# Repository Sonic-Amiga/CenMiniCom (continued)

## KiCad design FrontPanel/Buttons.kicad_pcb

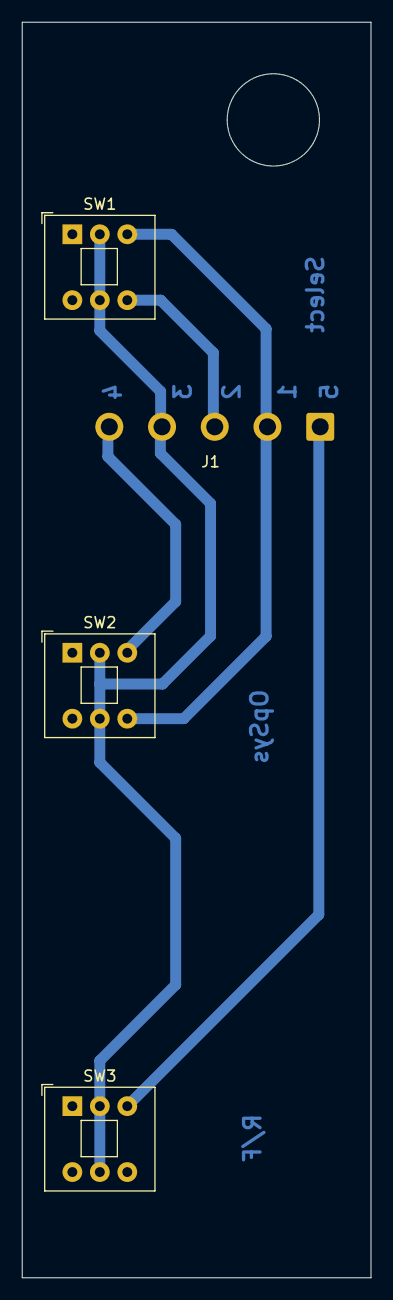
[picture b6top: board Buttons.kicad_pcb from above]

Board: 2 copper layers, 31.8 x 114.3 mm, 4 parts (0 on the bottom side), 5 nets.

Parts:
J1: Conn_01x05_Female; SolderWire-0.75sqmm_1x05_P4.8mm_D1.25mm_OD2.3mm
SW1: SELECT; SW_Push_2P2T_Toggle_CK_PVA2xxH1xxxxxxV2
SW2: OPSYS; SW_Push_2P2T_Toggle_CK_PVA2xxH1xxxxxxV2
SW3: R/F; SW_Push_2P2T_Toggle_CK_PVA2xxH1xxxxxxV2

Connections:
unnamed: J1.4, SW1.2 (B), SW1.5 (B), SW2.2 (B), SW2.5 (B), SW3.2 (B), SW3.5 (B)
unnamed: J1.2, SW1.3 (C), SW2.6 (C)
unnamed: J1.3, SW1.6 (C)
unnamed: J1.5, SW2.3 (C)
unnamed: J1.1, SW3.3 (C)

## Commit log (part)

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2022-08-10 CPU: Part replacement
    Some parts are not available, replaced with analogs
2022-08-11 CPU: Replace 8835
    This part isn't available at all; so let's replace it with ls240 + ls244. ls240
    looks the most electrically compatible in terms of current loads.
2022-08-15 Get rid of 74ls378
    This chip is rather rare and expensive here. Three can be replaced by 74ls379;
    use 74ls377 instead of the remaining one (ALU flags register)
    Analogs list populated and changed to a more proper encoding
2022-08-16 Replace edge connector with pin headers
2022-08-16 Attempt to fix a table
2022-08-17 CPU: Part placement
    Place parts on the board, no routing yet
2022-08-18 Fix ISA ROM designation
    Replace russian 'C' letter with latin one. They look identical but have
    different codes and UTF-8 characters in the .dsn file cause FreeRouting's
    loader to crash
2022-08-19 Manual layout WIP
    Attempt on manually-assisted layout. This uncovers some opportunities for
    optimization.
2022-08-19 Changed twist on uCode read buffers
    This yields much more optimal PCB layout
2022-08-20 More schematic optimizations:
    - Constant gate pins rearranged
    - Disconnected P7.14 from uROM override. The connector is located too far, the
    track is not convenient to route
2022-08-20 Changed U_M7 pin assignments
    Now lays out straight
2022-08-21 Another checkpoint
    Arranging the parts back does have some success, it's now time to try to replace
    some of them with SOIC.
2022-08-21 DIP layout prototype
    Parts arranged
2022-08-21 Part of routed layout
    A successful manually routed part: sequencer ROMs and buffers.
2022-08-21 Optimized connections around R7
    Removed debugging connections, switched pins around for straight tracks.
    Some inverters optimized away due to debug harness removal
2022-08-21 Revert back to Centurion edge connector
    Since i've found original connectors, there's no reason for substitution
2022-08-21 Some PoC routing near the bus connector
    A checkpoint, i'll try moving chips around in order to optimize tracks
2022-08-22 Routing WIP
    Checkpoint
2022-08-24 Some power lines
    Proof of concept - can i really do it ?
2022-08-25 Substitute RN16
    A dual 330+220 ohm resistor network appears to only be available in DIP package
    here; additionally having these resistors in one assembly requires more long
    traces, which are very inconvenient in connector area as both layers are quite
    busy. Break it down into individual parts.
2022-08-26 Swap U_B11C inputs
    Lays out much better
2022-08-28 Rounting WIP
    Second row almost done.
2022-08-28 Second row completed
2022-08-31 More layout
    3rd row ~75% completed
2022-09-01 4rth row placement
    PoC placement, optimized tracks layout, Result bus moved to the right side. A
    checkpoint before moving the whole row.
2022-09-01 Move completed
    Now we have much more space between 4th and 5th rows for tracks
2022-09-02 Remove P10
    This diagnostics connector gives direct access to page table DRAM, we don't need
    it. In fact it could have been located in B row with much shorter traces, but
    the only available position there is occupied by second ISA ROM half.
2022-09-03 Fixed U13H/U13L footprint
    Noticed in time and replaced with proper DIP16 instead of DIP20, erroneously
    left over from the original ROM
2022-09-03 4th row completed
2022-09-04 Bottom-left corner
    Restarted from another corner in order to better understand what spacing is
    needed.
2022-09-06 Routing WIP
    Sequencers and beginning of the ALU
2022-09-09 Routing WIP
    ALU completed, 1.5 rows left
2022-09-09 Move U_E12
    Place it next to P4, which it services. Much better layout.
2022-09-09 New P4 and U_E12
    Connect all the pins
2022-09-09 Split divider network RN4
    Separated into individual single-resistor components for routing optimization
    and easier access
2022-09-10 Power routing in progress
    About 60% connections succeeded
2022-09-11 Add jumper pads complete DRC
    Add jumper pads for completing GND and VCC by wires. DRC passes except
    unconnected nets of course
2022-09-11 Some more power connections
    Successfully router after a careful look
2022-09-11 Some layout optimization
    Moving R18 let us run some more straight connections
2022-09-11 One more connection
2022-09-12 Power and GND as poured layers
    In2 flood - GND
    In1 flood - +5V
2022-09-12 Clean up
    Clean up and complete DRC
2022-09-12 More power
    One connection to go
2022-09-13 Redundant power tracks
    Squeeze in parallel power distribution tracks where deemed possible. Power
    distribution should be significantly better, but solder-on pads are still
    provided.
2022-09-13 Clean up artifacts
    Fix some artifacts, like "split" track, found by factory's DRC.
2022-09-27 Finished MUX
    Merged in from Meisaka's repo
2022-10-02 Substitute 8835s
    Substitute unobtanium chips with 74ls240's
2022-10-02 Use 8-way DIP switch
    Let's not bother with upper half. It's always possible to install a smaller
    switch and hard-solder the upper half.
2022-10-03 MUX: Start of the layout
    Let's see how it goes...
2022-10-03 MUX: Place capacitors and some power layout
    Place decoupling capacitors and do some power layout to try it out
2022-10-04 MUX layout
    Work in progress
2022-10-06 MUX: Routing
    6 rows done
2022-10-08 MUX: Some schematic fixes
    - Proper U_K5 footprint
    - Fix 12V filter caps connection
2022-10-10 MUX: Update the layout
    Apply schematic corrections
2022-11-04 More chip analogs
    Populated analogs table with chips i've installed so far. Fixed mistake
    regarding 74LS37
2022-11-05 CPU: Fix a huuuge erratum
    CPU-E001: AMD SRAM chips use wide footprints (10.16 mm); a standard 7.62mm
    width was errorneously used instead
    This allows to slightly improve power layout by adding a couple more thick
    tracks.
2022-11-05 CPU: Fold back resistor arrays
    Get rid of lonely termination resistors; now only arrays of 4 and 8 are used.
    These should be more widespread.
2022-11-05 Some track rearrangement
    Relax some tight places for ease of soldering
2022-11-05 CPU: Fix C3 footprint
    Fix broken footprint (forgot to update footprints in the SCH)
2022-11-06 CPU: Add missing connection
    CPU-E002: Add missing connection between U_M10 pins 4 and 5.
2022-11-10 CPU: Some power layout optimizations
    Remove some vias, thicker traces in some places. Some other traces rearranged
    to accomodate changes
2022-11-10 CPU: Add important build info
    Restructured the documentation, there's now one file per board. Easier to read
    and maintain.
2022-11-10 MUX: Add connector pinout switch jumpers
    Provide jumper blocks to easily confiure MUX outputs as either Centuriobn native
    or standard RS232 pinout. Provides for ease of use of USB adapters,
    off-the-shelf cables, etc.
2022-11-11 MUX: Connections completed
    All traces done
2022-11-11 MUX: Fix DRC errors
    Rearranged U_E4 socket and extra row in order to avoid overlap errors. Fixed up
    jumper block courtyards.
2022-11-11 MUX: Move connectors
    Move connectors to the center in order to provide the necessary space for
    pullers.
2022-11-11 MUX: Clean up silkscreen and assembly notes around U_E4
    Fix DRC warnings, rearrange things to be more intuitive.
2022-11-24 CPU: Some more layout optimizations
    Removed some vias, straightened some tracks.
2022-11-25 FrontPanel: Initial schematic
    Redrawn (almost) as it was from the original diagram, made in DesignSpark, by
    Nakazoto.
2022-11-25 FrontPanel: Parts placement
    Placed all the parts close to original layout.
2022-11-25 FrontPanel: More glorification
    R/F switch inverter
2022-11-26 FrontPanel: Complete
    Add potentiometer to adjust clock frequency and better connector for buttons.
    Complete the layout.
2022-11-26 CPU: More layout improvements
    More small optimizations here and there, more ground widened to 2mm
2022-11-26 CPU: Erratum E003
    Found and fixed a missing connection
2022-11-26 CPU: More clean up
    Noticed some free space, left after the last optimization, and used it to move
    tracks further away from pads
2022-11-26 CPU: /DataReady reroute
    Reroute /DataReady from U_A3, kill one more via
2022-11-26 FrontPanel: Add backplane connector labels
    Add net labels for the backplane connector
2022-11-26 FrontPanel: Add missing mounting holes
    Got information on their placement, so put them in
2022-11-26 FrontPanel: Buttons board
    A preliminary design of a button board. Needs to be verified against actual
    parts footprint.
2022-11-27 Backplane: Completed
    Full board layout
2022-11-27 Document new boards
    Add README for backplane and front panel
2022-11-27 Backplane: Improve flooding
    Move some vias around to fill more area
2022-11-28 Backplane: Fix RA15 signal
    Original schematic by Nakazoto contained an error, which has been fixed. So no
    need for an experimental jumper on RA15 line; and 220-330 divider actually sits
    on a Reset signal, coming from the front panel.
2022-11-30 FrontPanel: Move tracks
    Move D13-D16 tracks away from R5.
2022-12-02 CPU: Updated README
    Complete chip analogs list
2022-12-06 MUX: Use axial capacitors
    Use axial capacitors in order to fully correspond to original board.
2022-12-16 Backplane: Use socket for U_A1
    Just for compliance, let's change U_A1 footprint to socket
2022-12-17 Backplane: Update footprint in the schematic
    Update footprint association, synchronize with the PCB. Add one more replacement
    entry to the README
2022-12-18 FrontPanel: Improve ground separation
    Follow the original idea and fully decouple GND from different connectors.
2022-12-19 FrontPanel: Increase J3 holes size
    Increase so that MPW connector actually fits in
2023-03-09 FrontPanel: Erratum E001
    Due to unverified assumptions in original schematic, power and ground separation
    between connectors, which is actually present on original boards, wasn't done
    correctly.
2023-08-01 DebugInterface: Redone with PIC18
    Better I/O ports and normal USB.
2023-08-27 DebugInterface: Some layout touchups
    Better copper fill
2023-09-12 DebugInterface: Fix ISP connector
    Proper pin assignment
2023-09-12 DebugInterface/Firmware: Reorganize project
    Squash paths
2025-03-05 Firmware/app: Protocol v1
    Better and more consistent USB protocol.
2025-03-05 Firmware/pio_bus: Fix bugs
    Breadoard version with a single 8255 works now
2025-03-11 DebugInterface: better PCB routing
2025-03-15 DebugInterface: Final preps
    A bit of layout optimization, LED designations on silkscreen
2025-03-16 DebugInterface: Last-minute corrections
    Spotted unconnected Rd line
2025-03-20 DiagBoard reconstruction
    Schematic of the original DiagBoard, redrawn as KiCad, with some unobtanium part
    replacements. Work in progress.
2025-03-23 Fix U_C8 type
    It's 74LS08
2025-03-23 DiagBoard: Elements placement
    Starting PCB preliminary routing, evaluated elements placement.
2025-03-23 DiagBoard: Untwist U_B3 lines
    Routes easier
2025-03-31 CPU: Even more layout optimizations
    More GND and +5V
2025-04-04 DiagBoard: Layout in progress
    WIP dump. SRAM chips need replacement.
2025-05-11 Firmware/app: Support multi-byte reads/writes
    Read/write sequentially starting from the given address. Up to 8 bytes.
2025-05-11 Firmware: Add usb framework
    Forgotten 'git add', so that the code can actually be compiled
2025-05-11 DebugInferface/Firmware: Enable activity LED
    We lo-o-o-o-ve blinkenlights!
2025-05-24 DiagBoard: Complete reconstruction
    Complete with extra functionality and connectors for experiments
2025-05-26 DiagBoard: Add memory delay selection jumper
    For experiments and fine-tuning.
2025-06-11 MUX: Info, fixes
    - Complete chip replacement list
    - Fix SN75150 symbol appearance
2025-07-09 DiagBoard: Add /RESET to experimental connector
    Can be useful
